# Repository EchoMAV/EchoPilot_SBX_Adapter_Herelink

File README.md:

Created using KiCad 7.0.10

This is an open-source radio adapter designed for the EchoPilot SBX series of boards. It is meant for a Herelink v1.1+ air unit, but can also be used for serial telemetry and IP radios such as the RFD900 or Doodle Labs.

The board provides regulated 7.5VDC @ 2A

6 Layer PCB, 4/4 mil spacing, min hole size is 0.2mm Note impedance controlled traces for MIPI, USB and Ethernet. Trace width and spacing may need to be adjusted depending on the stackup and materials used in production.

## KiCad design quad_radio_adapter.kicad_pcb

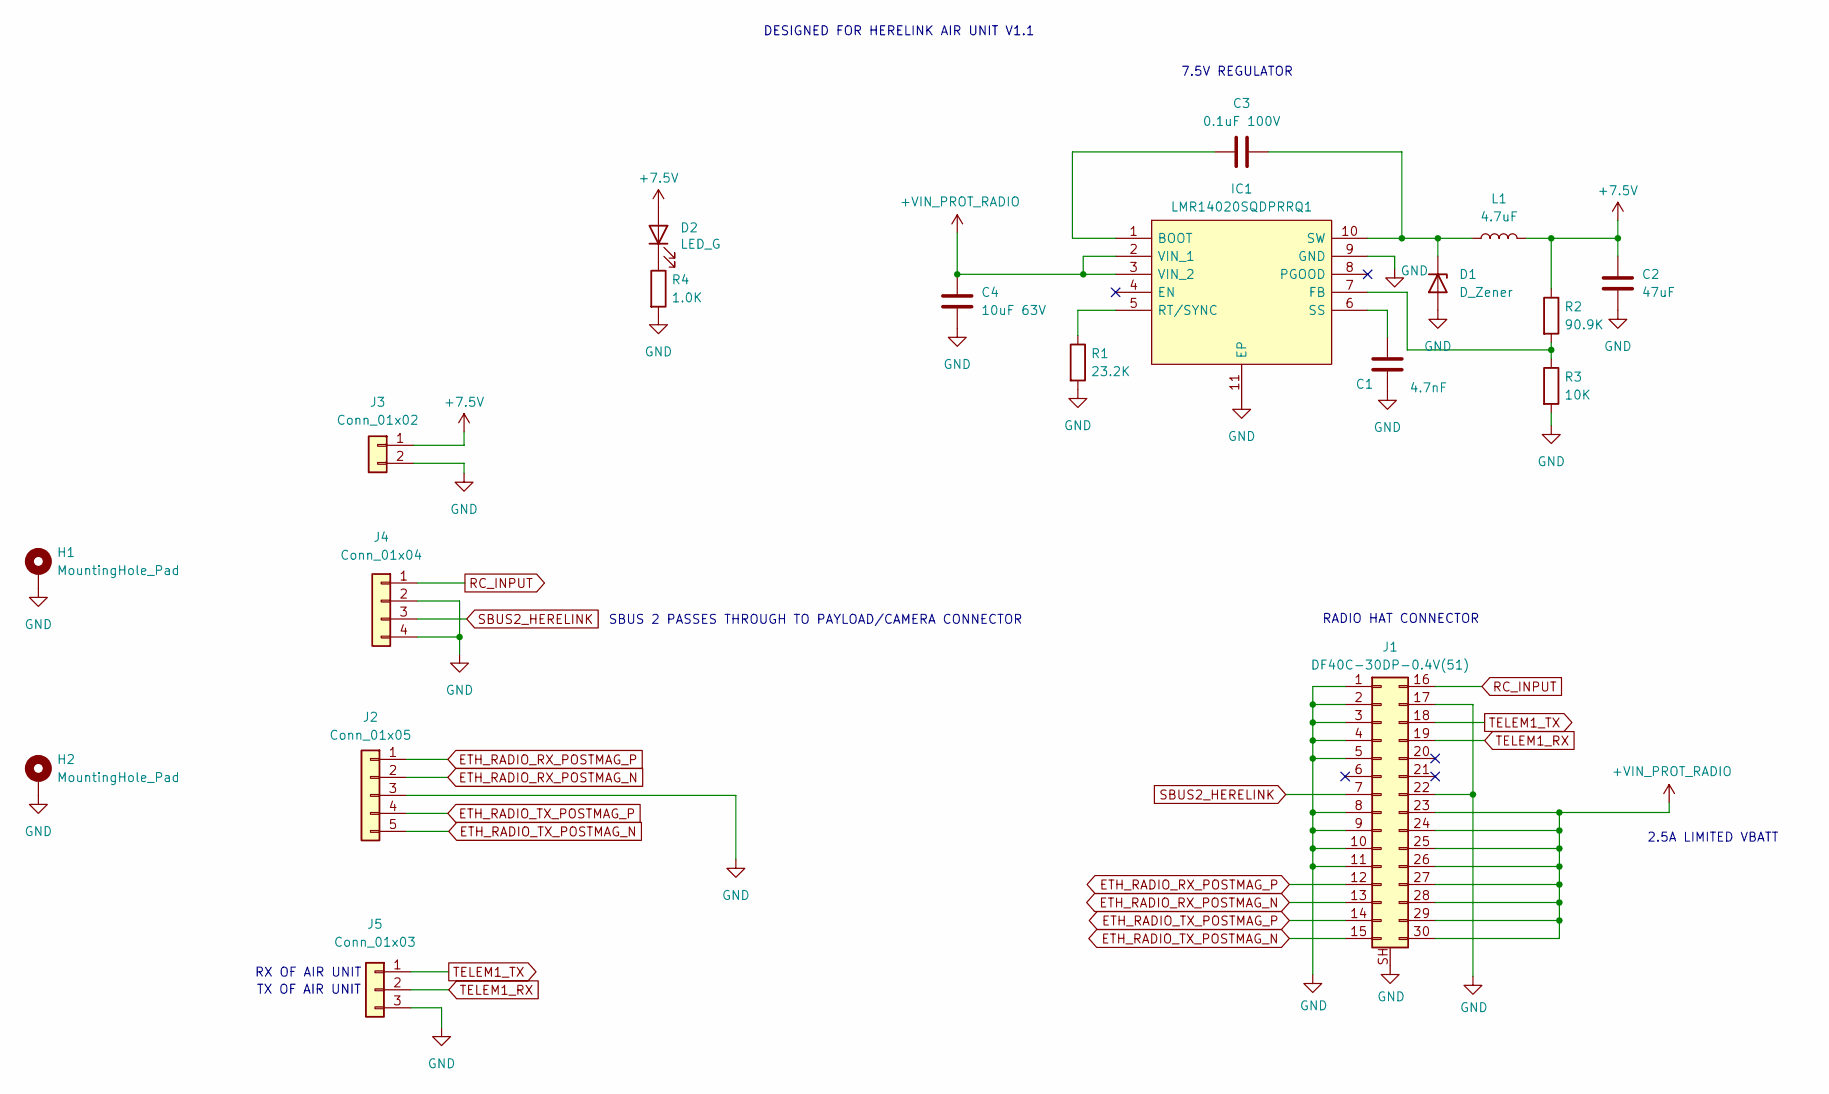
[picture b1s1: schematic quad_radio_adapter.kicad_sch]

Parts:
C1: 4.7nF; C_0201_0603Metric; Part Num GRM033R61E472KA12D
C2: 47uF; C_1206_3216Metric; Part Num C3216X5R1E476M160AC
C3: 0.1uF 100V; C_0603_1608Metric; Part Num CL10B104KC8NNNC
C4: 10uF 63V; C_1210_3225Metric; Part Num CL32B106KMVNNWE
D1: D_Zener; D_SMA; Part Num SK220A
D2: LED_G; LED_0603_1608Metric; Part Num 150060VS75000
H1, H2: MountingHole_Pad; MountingHole_2.2mm_M2_Pad
IC1: LMR14020SQDPRRQ1; SON80P400X400X80-11N; Manufacturer_Part_Number LMR14020SQDPRRQ1; Mouser Part Number 595-LMR14020SQDPRRQ1
J1: DF40C-30DP-0.4V(51); HRS_DF40C-30DP-0.4V_51_; Part Num DF40C-30DP-0.4V(51)
J2: Conn_01x05; JST_GH_SM05B-GHS-TB_1x05-1MP_P1.25mm_Horizontal; Part Num SM05B-GHS-TBT
J3: Conn_01x02; JST_GH_SM02B-GHS-TB_1x02-1MP_P1.25mm_Horizontal; Part Num SM02B-GHS-TBT
J4: Conn_01x04; JST_GH_SM04B-GHS-TB_1x04-1MP_P1.25mm_Horizontal; Part Num SM04B-GHS-TBT
J5: Conn_01x03; JST_GH_SM03B-GHS-TB_1x03-1MP_P1.25mm_Horizontal; Part Num SM03B-GHS-TBT
L1: 4.7uF; IND_336047_WRE; Part Num 74438336047
R1: 23.2K; R_0201_0603Metric; Part Num ERJ-1GNF2322C
R2: 90.9K; R_0201_0603Metric; Part Num ERJ-1GNF9092C
R3: 10K; R_0201_0603Metric; Part Num ERJ-1GNF1002C
R4: 1.0K; R_0201_0603Metric; Part Num ERJ-1GEF1001C

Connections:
+7.5V: C2.1, D2.2 (A), J3.1, L1.2, R2.1
+VIN_PROT_RADIO: C4.1, IC1.2 (VIN_1), IC1.3 (VIN_2), J1.23, J1.24, J1.25, J1.26, J1.27, J1.28, J1.29, J1.30
ETH_RADIO_RX_POSTMAG_N: J1.13, J2.2
ETH_RADIO_RX_POSTMAG_P: J1.12, J2.1
ETH_RADIO_TX_POSTMAG_N: J1.15, J2.5
ETH_RADIO_TX_POSTMAG_P: J1.14, J2.4
GND: C1.2, C2.2, C4.2, D1.2 (A), H1.1, H2.1, IC1.9 (GND), IC1.11 (EP), J1.1, J1.2, J1.3, J1.4, J1.5, J1.8, J1.9, J1.10, J1.11, J1.17, J1.22, J1.SH, J2.3, J3.2, J4.2, J4.4, J5.3, R1.2, R3.2, R4.2
unnamed: C3.2, D1.1 (K), IC1.10 (SW), L1.1
unnamed: D2.1 (K), R4.1
unnamed: C3.1, IC1.1 (BOOT)
unnamed: IC1.7 (FB), R2.2, R3.1
unnamed: IC1.5 (RT/SYNC), R1.1
unnamed: C1.1, IC1.6 (SS)
RC_INPUT: J1.16, J4.1
SBUS2_HERELINK: J1.7, J4.3
TELEM1_RX: J1.19, J5.2
TELEM1_TX: J1.18, J5.1

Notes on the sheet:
RX OF AIR UNIT
7.5V REGULATOR
2.5A LIMITED VBATT
RADIO HAT CONNECTOR
TX OF AIR UNIT
SBUS 2 PASSES THROUGH TO PAYLOAD/CAMERA CONNECTOR
DESIGNED FOR HERELINK AIR UNIT V1.1

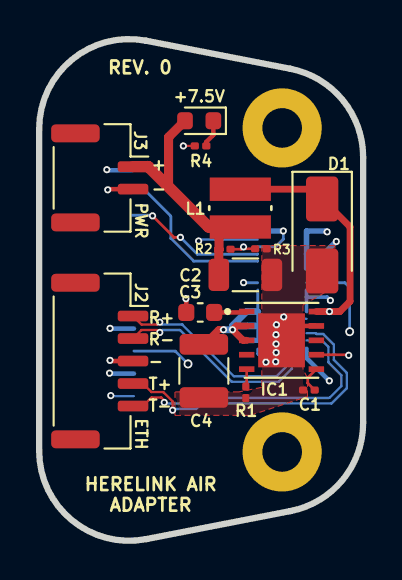
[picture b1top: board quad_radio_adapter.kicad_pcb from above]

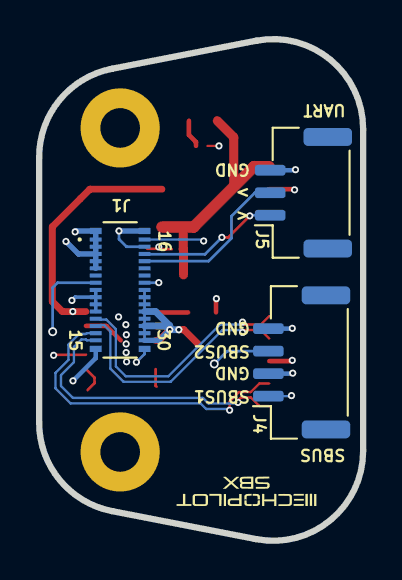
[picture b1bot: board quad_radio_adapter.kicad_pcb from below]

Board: 6 copper layers, 18.0 x 27.9 mm, 19 parts (3 on the bottom side), 17 nets.

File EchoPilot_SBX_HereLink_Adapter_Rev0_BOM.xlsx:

EchoPilot SBX HereLink Radio Adapter Rev 0
Item | Qty | Reference(s) | Value | LibPart | Footprint | Part Num
1 | 1 | C1 | 4.7nF | Device:C | Capacitor_SMD:C_0201_0603Metric | GRM033R61E472KA12D
2 | 1 | C2 | 47uF | Device:C | Capacitor_SMD:C_1206_3216Metric | C3216X5R1E476M160AC
3 | 1 | C3 | 0.1uF 100V | Device:C | Capacitor_SMD:C_0603_1608Metric | CL10B104KC8NNNC
4 | 1 | C4 | 10uF 63V | Device:C | Capacitor_SMD:C_1210_3225Metric | CL32B106KMVNNWE
5 | 1 | D1 | D_Zener | Device:D_Zener | Diode_SMD:D_SMA | SK220A
6 | 1 | D2 | LED_G | Device:LED | LED_SMD:LED_0603_1608Metric | 150060VS75000
7 | 1 | IC1 | LMR14020SQDPRRQ1 | LMR14020SQDPRRQ1:LMR14020SQDPRRQ1 | SON80P400X400X80-11N | LMR14020SQDPRRQ1
8 | 1 | J1 | DF40C-30DP-0.4V(51) | Connector_Generic:Conn_02x15_Top_Bottom | UVDL.Pretty:HRS_DF40C-30DP-0.4V_51_ | DF40C-30DP-0.4V(51)
9 | 1 | J2 | Conn_01x05 | Connector_Generic:Conn_01x05 | Connector_JST:JST_GH_SM05B-GHS-TB_1x05-1MP_P1.25mm_Horizontal | SM05B-GHS-TBT
10 | 1 | J3 | Conn_01x02 | Connector_Generic:Conn_01x02 | Connector_JST:JST_GH_SM02B-GHS-TB_1x02-1MP_P1.25mm_Horizontal | SM02B-GHS-TBT
11 | 1 | J4 | Conn_01x04 | Connector_Generic:Conn_01x04 | Connector_JST:JST_GH_SM04B-GHS-TB_1x04-1MP_P1.25mm_Horizontal | SM04B-GHS-TBT
12 | 1 | J5 | Conn_01x03 | Connector_Generic:Conn_01x03 | Connector_JST:JST_GH_SM03B-GHS-TB_1x03-1MP_P1.25mm_Horizontal | SM03B-GHS-TBT
13 | 1 | L1 | 4.7uF | Device:L | UVDL.Pretty:IND_336047_WRE | 74438336047
14 | 1 | R1 | 23.2K | Device:R | Resistor_SMD:R_0201_0603Metric | ERJ-1GNF2322C
15 | 1 | R2 | 90.9K | Device:R | Resistor_SMD:R_0201_0603Metric | ERJ-1GNF9092C
16 | 1 | R3 | 10K | Device:R | Resistor_SMD:R_0201_0603Metric | ERJ-1GNF1002C
17 | 1 | R4 | 1.0K | Device:R | Resistor_SMD:R_0201_0603Metric | ERJ-1GEF1001C

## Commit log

2024-02-02 initial
